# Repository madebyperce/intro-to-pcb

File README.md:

# intro-to-pcb
 Following ai03's guide to design PCBs!

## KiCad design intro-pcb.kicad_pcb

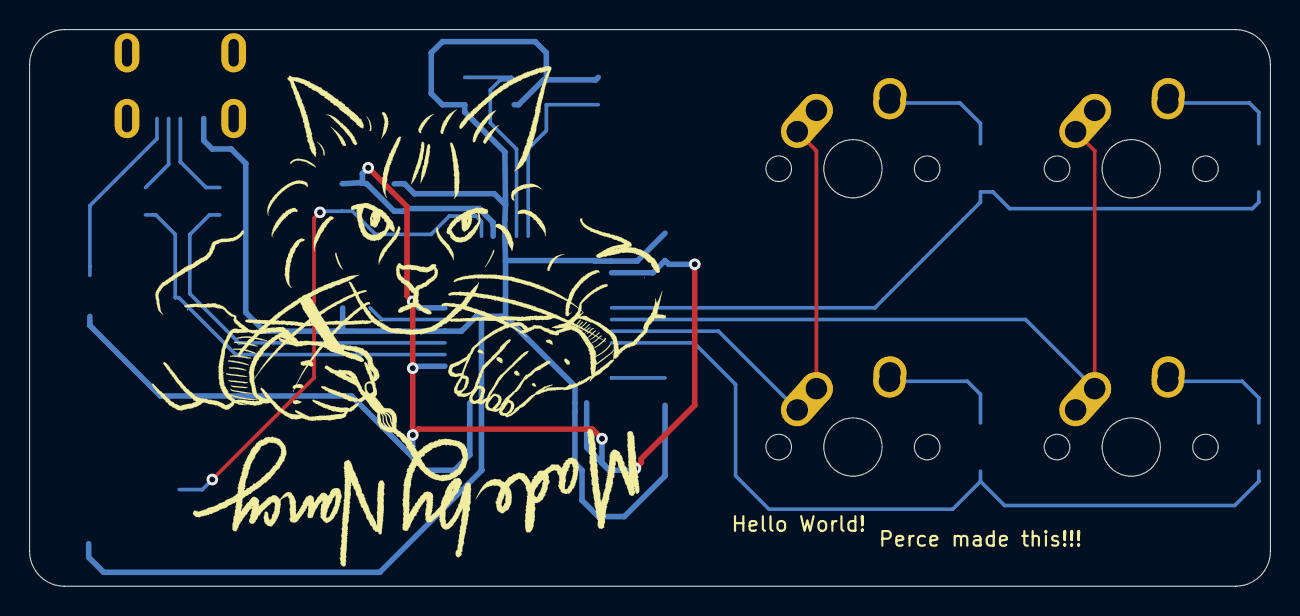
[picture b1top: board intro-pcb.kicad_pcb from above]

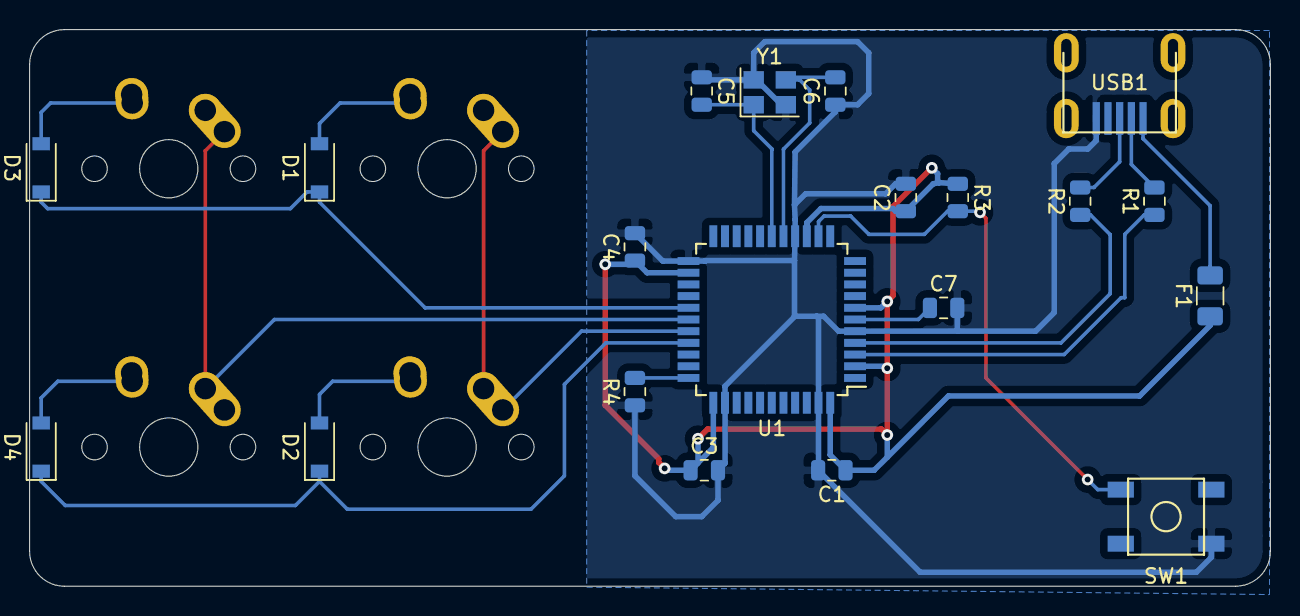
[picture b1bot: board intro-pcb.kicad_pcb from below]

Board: 2 copper layers, 84.9 x 38.1 mm, 24 parts (20 on the bottom side), 20 nets.

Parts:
C1, C2, C3, C4: 0.1uf; C_0805_2012Metric
C5, C6: 22pF; C_0805_2012Metric
C7: 1uF; C_0805_2012Metric
D1, D2, D3, D4: D_Small; D_SOD-123
F1: 500mA; Fuse_1206_3216Metric
MX1, MX2, MX3, MX4: MX-NoLED; MX-1U-NoLED
R1, R2: 22; R_0805_2012Metric
R3, R4: 10k; R_0805_2012Metric
SW1: SW_Push; SKQG-1155865
U1: ATmega32U4-AU; TQFP-44_10x10mm_P0.8mm
USB1: Molex-0548190589
Y1: Crystal_GND24_Small; Crystal_SMD_3225-4Pin_3.2x2.5mm

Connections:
+5V: C1.1, C2.1, C3.1, C4.1, F1.1, R3.1, U1.2, U1.7, U1.14, U1.24, U1.34, U1.44
COL0: MX1.1, MX2.1, U1.29
COL1: MX3.1, MX4.1, U1.28
D+: R2.2, USB1.3
D-: R1.2, USB1.4
GND: C1.2, C2.2, C3.2, C4.2, C5.1, C6.1, C7.2, R4.1, SW1.1, U1.5, U1.15, U1.23, U1.35, U1.43, USB1.1, Y1.2, Y1.4
unnamed: C5.2, U1.17, Y1.1
unnamed: C6.2, U1.16, Y1.3
unnamed: C7.1, U1.6
unnamed: D1.2, MX1.2
unnamed: D2.2, MX2.2
unnamed: D3.2, MX3.2
unnamed: D4.2, MX4.2
unnamed: R1.1, U1.3
unnamed: R2.1, U1.4
unnamed: R3.2, SW1.2, U1.13
unnamed: R4.2, U1.33
ROW0: D1.1, D3.1, U1.27
ROW1: D2.1, D4.1, U1.30
VCC: F1.2, USB1.5

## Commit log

2021-04-08 first commit!
2021-04-08 Add submodules
2021-04-08 update with libraries
2021-04-09 update schematic
2021-04-16 Added traces
2021-04-16 Generate Gerbers
